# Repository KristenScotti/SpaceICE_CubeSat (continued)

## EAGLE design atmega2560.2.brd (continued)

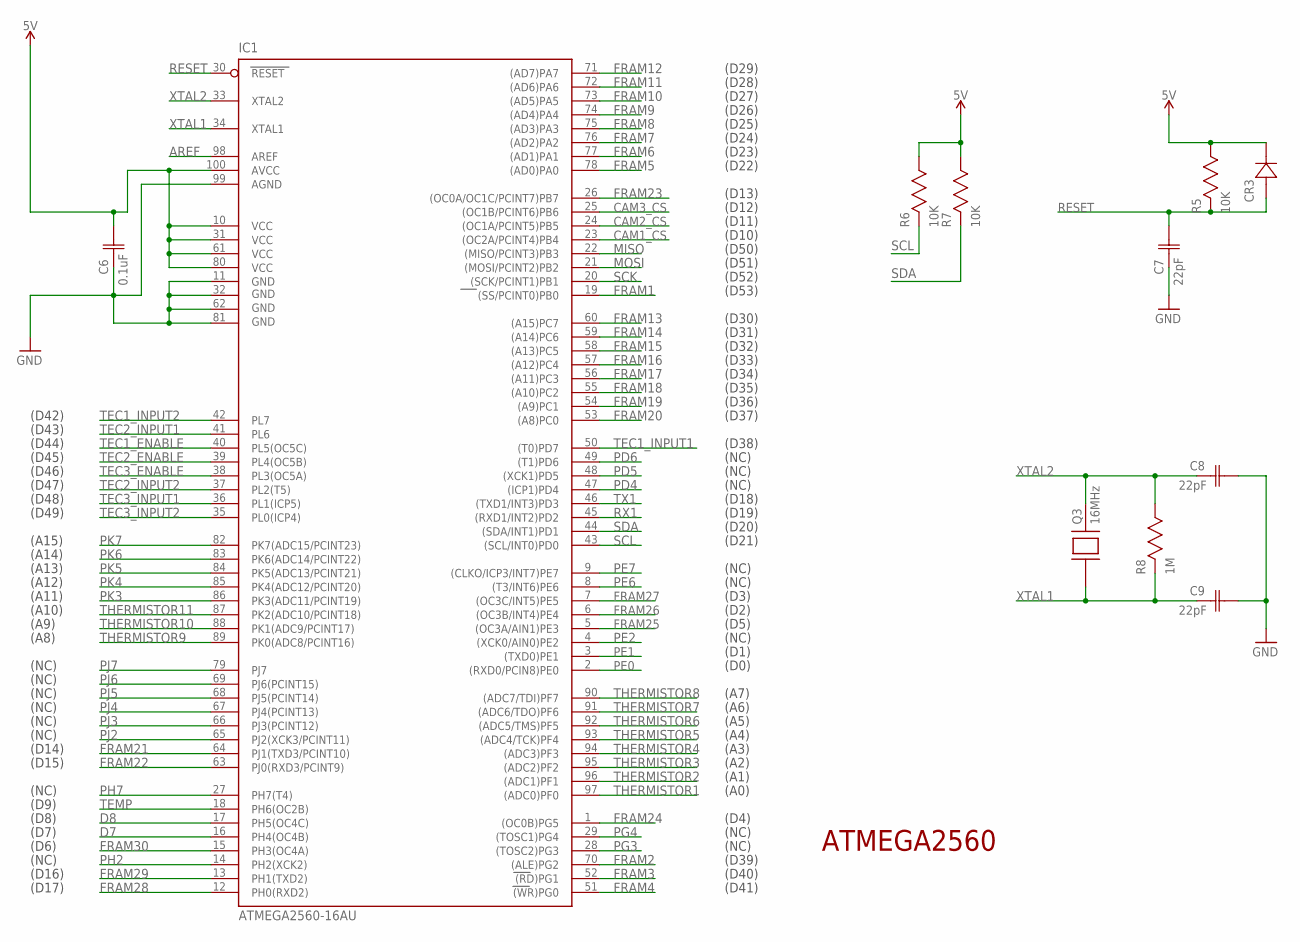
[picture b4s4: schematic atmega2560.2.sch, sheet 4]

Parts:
C6: 0.1uF; CAP_01
C7, C8, C9: 22pF; CC0805N
CR3: DIODE_600V_3A
IC1: ATMEGA2560-16AU; TQFP100
Q3: 16MHz; OSCILLATOR
R5, R6, R7: 10K; RC0603N
R8: 1M; RC0603N

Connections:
5V: C6.2, CR3.1 (12), IC1.10 (VCC), IC1.31 (VCC1), IC1.61 (VCC2), IC1.80 (VCC3), IC1.100 (AVCC), R5.1 (11), R6.1 (11), R7.1 (11); also elsewhere on the board
AREF: IC1.98 (AREF); also elsewhere on the board
CAM1_CS: IC1.23 ((OC2A/PCINT4)PB4); also elsewhere on the board
CAM2_CS: IC1.24 ((OC1A/PCINT5)PB5); also elsewhere on the board
CAM3_CS: IC1.25 ((OC1B/PCINT6)PB6); also elsewhere on the board
D7: IC1.16 (PH4(OC4B)); also elsewhere on the board
D8: IC1.17 (PH5(OC4C)); also elsewhere on the board
FRAM1: IC1.19 ((SS/PCINT0)PB0); also elsewhere on the board
FRAM2: IC1.70 ((ALE)PG2); also elsewhere on the board
FRAM3: IC1.52 ((RD)PG1); also elsewhere on the board
FRAM4: IC1.51 ((WR)PG0); also elsewhere on the board
FRAM5: IC1.78 ((AD0)PA0); also elsewhere on the board
FRAM6: IC1.77 ((AD1)PA1); also elsewhere on the board
FRAM7: IC1.76 ((AD2)PA2); also elsewhere on the board
FRAM8: IC1.75 ((AD3)PA3); also elsewhere on the board
FRAM9: IC1.74 ((AD4)PA4); also elsewhere on the board
FRAM10: IC1.73 ((AD5)PA5); also elsewhere on the board
FRAM11: IC1.72 ((AD6)PA6); also elsewhere on the board
FRAM12: IC1.71 ((AD7)PA7); also elsewhere on the board
FRAM13: IC1.60 ((A15)PC7); also elsewhere on the board
FRAM14: IC1.59 ((A14)PC6); also elsewhere on the board
FRAM15: IC1.58 ((A13)PC5); also elsewhere on the board
FRAM16: IC1.57 ((A12)PC4); also elsewhere on the board
FRAM17: IC1.56 ((A11)PC3); also elsewhere on the board
FRAM18: IC1.55 ((A10)PC2); also elsewhere on the board
FRAM19: IC1.54 ((A9)PC1); also elsewhere on the board
FRAM20: IC1.53 ((A8)PC0); also elsewhere on the board
FRAM21: IC1.64 (PJ1(TXD3/PCINT10)); also elsewhere on the board
FRAM22: IC1.63 (PJ0(RXD3/PCINT9)); also elsewhere on the board
FRAM23: IC1.26 ((OC0A/OC1C/PCINT7)PB7); also elsewhere on the board
FRAM24: IC1.1 ((OC0B)PG5); also elsewhere on the board
FRAM25: IC1.5 ((OC3A/AIN1)PE3); also elsewhere on the board
FRAM26: IC1.6 ((OC3B/INT4)PE4); also elsewhere on the board
FRAM27: IC1.7 ((OC3C/INT5)PE5); also elsewhere on the board
FRAM28: IC1.12 (PH0(RXD2)); also elsewhere on the board
FRAM29: IC1.13 (PH1(TXD2)); also elsewhere on the board
FRAM30: IC1.15 (PH3(OC4A)); also elsewhere on the board
GND: C6.1, C7.1, C8.2, C9.2, IC1.11 (GND), IC1.32 (GND1), IC1.62 (GND2), IC1.81 (GND3), IC1.99 (AGND); also elsewhere on the board
MISO: IC1.22 ((MISO/PCINT3)PB3); also elsewhere on the board
MOSI: IC1.21 ((MOSI/PCINT2)PB2); also elsewhere on the board
PD4: IC1.47 ((ICP1)PD4)
PD5: IC1.48 ((XCK1)PD5)
PD6: IC1.49 ((T1)PD6)
PE0: IC1.2 ((RXD0/PCIN8)PE0); also elsewhere on the board
PE1: IC1.3 ((TXD0)PE1); also elsewhere on the board
PE2: IC1.4 ((XCK0/AIN0)PE2)
PE6: IC1.8 ((T3/INT6)PE6)
PE7: IC1.9 ((CLKO/ICP3/INT7)PE7)
PG3: IC1.28 ((TOSC2)PG3)
PG4: IC1.29 ((TOSC1)PG4)
PH2: IC1.14 (PH2(XCK2))
PH7: IC1.27 (PH7(T4))
PJ2: IC1.65 (PJ2(XCK3/PCINT11))
PJ3: IC1.66 (PJ3(PCINT12))
PJ4: IC1.67 (PJ4(PCINT13))
PJ5: IC1.68 (PJ5(PCINT14))
PJ6: IC1.69 (PJ6(PCINT15))
PJ7: IC1.79 (PJ7)
PK3: IC1.86 (PK3(ADC11/PCINT19)); also elsewhere on the board
PK4: IC1.85 (PK4(ADC12/PCINT20)); also elsewhere on the board
PK5: IC1.84 (PK5(ADC13/PCINT21)); also elsewhere on the board
PK6: IC1.83 (PK6(ADC14/PCINT22)); also elsewhere on the board
PK7: IC1.82 (PK7(ADC15/PCINT23)); also elsewhere on the board
RESET: C7.2, CR3.2 (21), IC1.30 (RESET), R5.2 (22); also elsewhere on the board
RX1: IC1.45 ((RXD1/INT2)PD2); also elsewhere on the board
SCK: IC1.20 ((SCK/PCINT1)PB1); also elsewhere on the board
SCL: IC1.43 ((SCL/INT0)PD0), R6.2 (22); also elsewhere on the board
SDA: IC1.44 ((SDA/INT1)PD1), R7.2 (22); also elsewhere on the board
TEC1_ENABLE: IC1.40 (PL5(OC5C)); also elsewhere on the board
TEC1_INPUT1: IC1.50 ((T0)PD7); also elsewhere on the board
TEC1_INPUT2: IC1.42 (PL7); also elsewhere on the board
TEC2_ENABLE: IC1.39 (PL4(OC5B)); also elsewhere on the board
TEC2_INPUT1: IC1.41 (PL6); also elsewhere on the board
TEC2_INPUT2: IC1.37 (PL2(T5)); also elsewhere on the board
TEC3_ENABLE: IC1.38 (PL3(OC5A)); also elsewhere on the board
TEC3_INPUT1: IC1.36 (PL1(ICP5)); also elsewhere on the board
TEC3_INPUT2: IC1.35 (PL0(ICP4)); also elsewhere on the board
TEMP: IC1.18 (PH6(OC2B)); also elsewhere on the board
THERMISTOR1: IC1.97 ((ADC0)PF0); also elsewhere on the board
THERMISTOR2: IC1.96 ((ADC1)PF1); also elsewhere on the board
THERMISTOR3: IC1.95 ((ADC2)PF2); also elsewhere on the board
THERMISTOR4: IC1.94 ((ADC3)PF3); also elsewhere on the board
THERMISTOR5: IC1.93 ((ADC4/TCK)PF4); also elsewhere on the board
THERMISTOR6: IC1.92 ((ADC5/TMS)PF5); also elsewhere on the board
THERMISTOR7: IC1.91 ((ADC6/TDO)PF6); also elsewhere on the board
THERMISTOR8: IC1.90 ((ADC7/TDI)PF7); also elsewhere on the board
THERMISTOR9: IC1.89 (PK0(ADC8/PCINT16)); also elsewhere on the board
THERMISTOR10: IC1.88 (PK1(ADC9/PCINT17)); also elsewhere on the board
THERMISTOR11: IC1.87 (PK2(ADC10/PCINT18)); also elsewhere on the board
TX1: IC1.46 ((TXD1/INT3)PD3); also elsewhere on the board
XTAL1: C9.1, IC1.34 (XTAL1), Q3.1, R8.2 (22)
XTAL2: C8.1, IC1.33 (XTAL2), Q3.2, R8.1 (11)

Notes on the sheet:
ATMEGA2560
(D4)
(D39)
(D40)
(D41)
(A0)
(D0)
(D3)
(D2)
(D5)
(D1)
(D21)
(D18)
(D19)
(D20)
(NC)
(D38)
(D37)
(D32)
(D33)
(D34)
(D35)
(D36)
(D31)
(D30)
(D53)
(D11)
(D10)
(D50)
(D51)
(D52)
(D12)
(D13)
(D22)
(D27)
(D26)
(D25)
(D24)
(D23)
(D28)

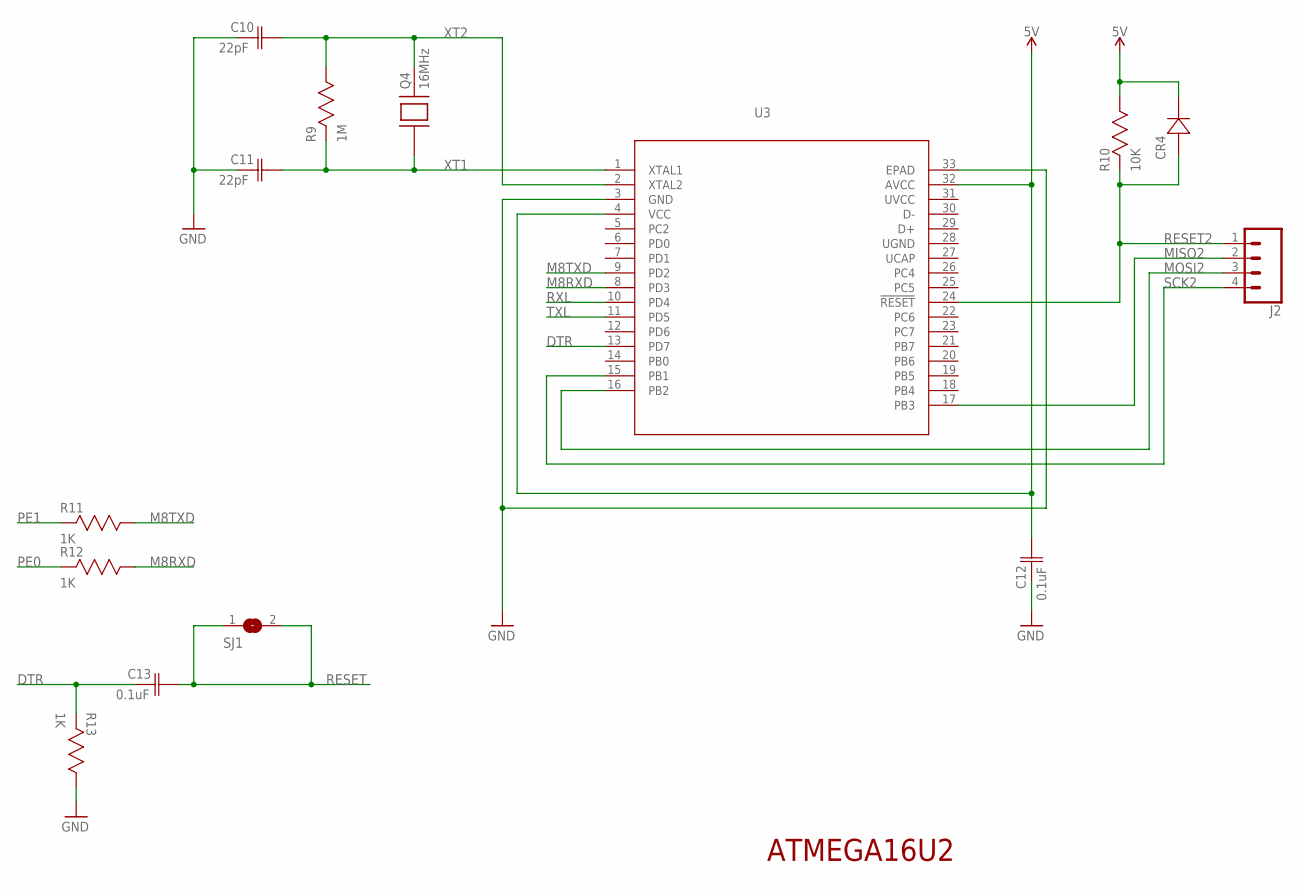
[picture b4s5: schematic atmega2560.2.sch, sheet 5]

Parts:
C10, C11: 22pF; CC0805N
C12, C13: 0.1uF; CAP_01
CR4: DIODE_600V_3A
J2: CONN_04; 1X04
Q4: 16MHz; OSCILLATOR
R9: 1M; RC0603N
R10: 10K; RC0603N
R11, R12, R13: 1K; RC0603N
SJ1: SJ
U3: ATMEGA16U2-MU; 32M1-A

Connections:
5V: C12.2, CR4.1 (12), R10.1 (11), U3.4 (VCC), U3.32 (AVCC); also elsewhere on the board
DTR: C13.1, R13.2 (22), U3.13 (PD7)
GND: C10.1, C11.1, C12.1, R13.1 (11), U3.3 (GND), U3.33 (EPAD); also elsewhere on the board
M8RXD: R12.1 (11), U3.8 (PD3)
M8TXD: R11.1 (11), U3.9 (PD2)
MISO2: J2.2, U3.17 (PB3)
MOSI2: J2.3, U3.16 (PB2)
PE0: R12.2 (22); also elsewhere on the board
PE1: R11.2 (22); also elsewhere on the board
RESET: C13.2, SJ1.1, SJ1.2; also elsewhere on the board
RESET2: CR4.2 (21), J2.1, R10.2 (22), U3.24 (!RESET)
RXL: U3.10 (PD4)
SCK2: J2.4, U3.15 (PB1)
TXL: U3.11 (PD5)
UGND: U3.28 (UGND)
UVCC: U3.31 (UVCC)
XT1: C11.2, Q4.1, R9.2 (22), U3.1 (XTAL1)
XT2: C10.2, Q4.2, R9.1 (11), U3.2 (XTAL2)

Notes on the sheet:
ATMEGA16U2

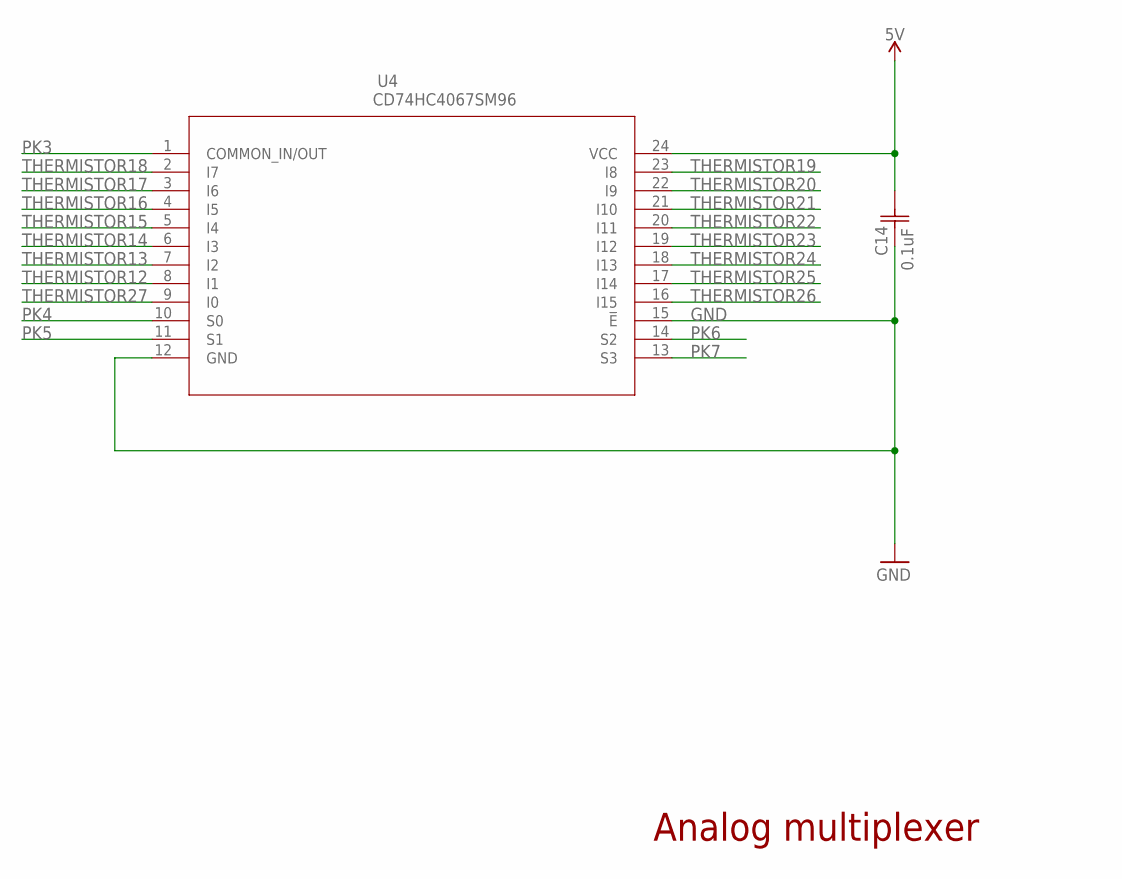
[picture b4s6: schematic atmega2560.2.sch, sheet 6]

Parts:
C14: 0.1uF; CAP_01
U4: CD74HC4067SM96; DB24

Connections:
5V: C14.2, U4.24 (VCC); also elsewhere on the board
GND: C14.1, U4.12 (GND), U4.15 (!E); also elsewhere on the board
PK3: U4.1 (COMMON_IN/OUT); also elsewhere on the board
PK4: U4.10 (S0); also elsewhere on the board
PK5: U4.11 (S1); also elsewhere on the board
PK6: U4.14 (S2); also elsewhere on the board
PK7: U4.13 (S3); also elsewhere on the board
THERMISTOR12: U4.8 (I1); also elsewhere on the board
THERMISTOR13: U4.7 (I2); also elsewhere on the board
THERMISTOR14: U4.6 (I3); also elsewhere on the board
THERMISTOR15: U4.5 (I4); also elsewhere on the board
THERMISTOR16: U4.4 (I5); also elsewhere on the board
THERMISTOR17: U4.3 (I6); also elsewhere on the board
THERMISTOR18: U4.2 (I7); also elsewhere on the board
THERMISTOR19: U4.23 (I8); also elsewhere on the board
THERMISTOR20: U4.22 (I9); also elsewhere on the board
THERMISTOR21: U4.21 (I10); also elsewhere on the board
THERMISTOR22: U4.20 (I11); also elsewhere on the board
THERMISTOR23: U4.19 (I12); also elsewhere on the board
THERMISTOR24: U4.18 (I13); also elsewhere on the board
THERMISTOR25: U4.17 (I14); also elsewhere on the board
THERMISTOR26: U4.16 (I15); also elsewhere on the board
THERMISTOR27: U4.9 (I0); also elsewhere on the board

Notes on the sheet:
Analog multiplexer

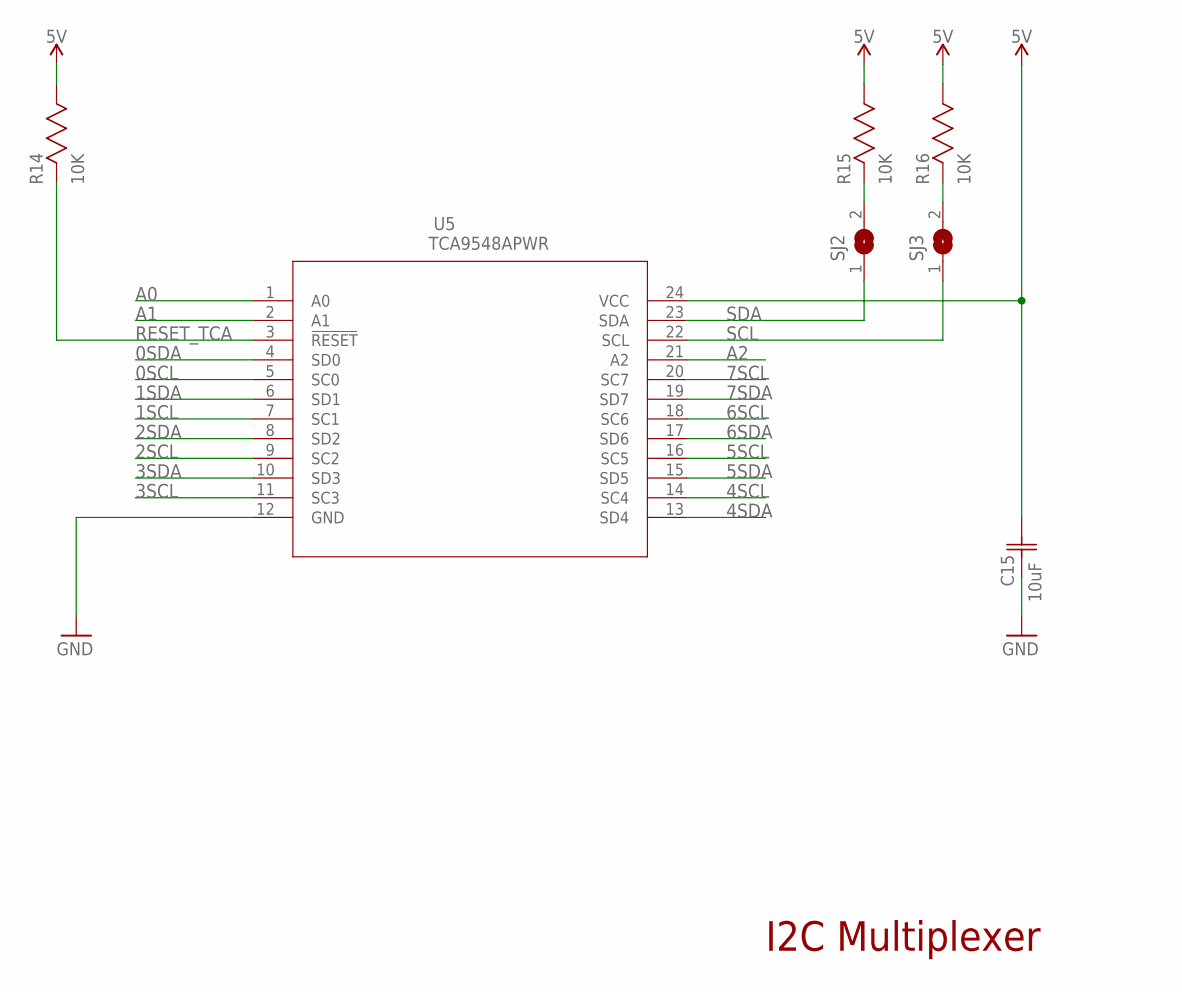
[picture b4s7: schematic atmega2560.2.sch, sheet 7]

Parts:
C15: 10uF; CAP_GRM219R61A106KE44D
R14, R15, R16: 10K; RC0603N
SJ2, SJ3: SOLDERJUMPERCLOSED; SOLDERJUMPER_CLOSEDWIRE
U5: TCA9548APWR; PW24

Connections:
0SCL: U5.5 (SC0); also elsewhere on the board
0SDA: U5.4 (SD0); also elsewhere on the board
1SCL: U5.7 (SC1); also elsewhere on the board
1SDA: U5.6 (SD1); also elsewhere on the board
2SCL: U5.9 (SC2); also elsewhere on the board
2SDA: U5.8 (SD2); also elsewhere on the board
3SCL: U5.11 (SC3)
3SDA: U5.10 (SD3)
4SCL: U5.14 (SC4)
4SDA: U5.13 (SD4)
5SCL: U5.16 (SC5)
5SDA: U5.15 (SD5)
5V: C15.2, R14.1 (11), R15.1 (11), R16.1 (11), U5.24 (VCC); also elsewhere on the board
6SCL: U5.18 (SC6)
6SDA: U5.17 (SD6)
7SCL: U5.20 (SC7)
7SDA: U5.19 (SD7)
A0: U5.1 (A0)
A1: U5.2 (A1)
A2: U5.21 (A2)
GND: C15.1, U5.12 (GND); also elsewhere on the board
unnamed: R15.2 (22), SJ2.2
unnamed: R16.2 (22), SJ3.2
RESET_TCA: R14.2 (22), U5.3 (!RESET)
SCL: SJ3.1, U5.22 (SCL); also elsewhere on the board
SDA: SJ2.1, U5.23 (SDA); also elsewhere on the board

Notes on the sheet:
I2C Multiplexer

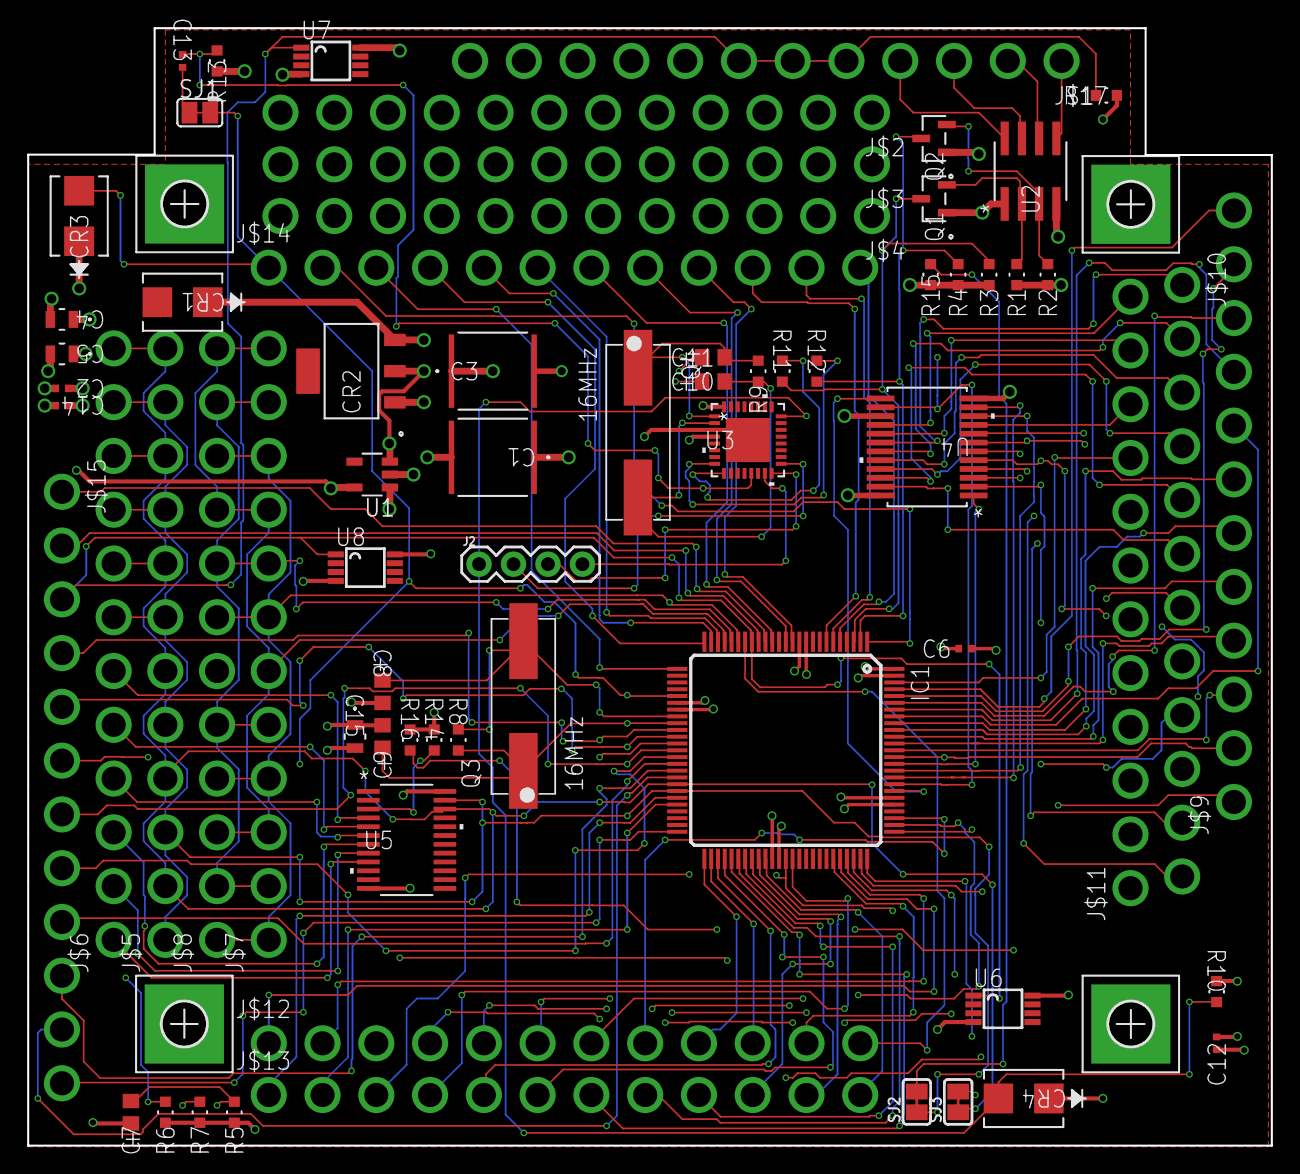
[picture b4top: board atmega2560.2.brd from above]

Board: 4 copper layers, 91.6 x 82.3 mm, 72 parts (0 on the bottom side), 118 nets.

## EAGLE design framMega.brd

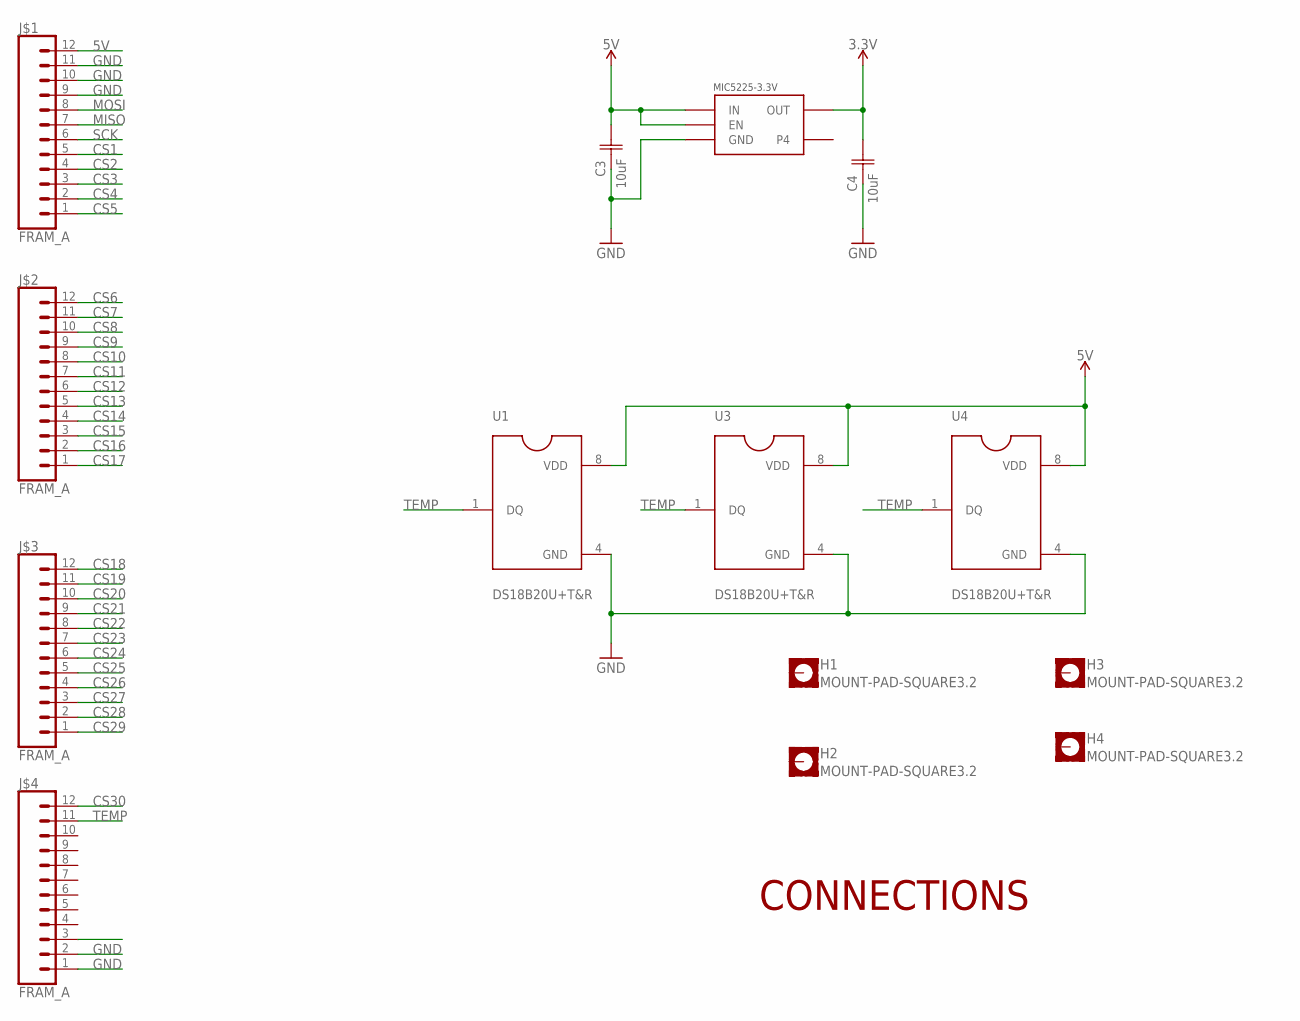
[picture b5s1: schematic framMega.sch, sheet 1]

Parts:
C3, C4: 10uF; CAP_GRM219R61A106KE44D
H1, H2, H3, H4: MOUNT-PAD-SQUARE3.2; 3,2-PAD-SQUARE
J$1, J$2, J$3, J$4: FRAM_A; WIREWRAPPOST
U1, U3, U4: DS18B20U+T&R; SOP65P500X110-8N
U2: MIC5225; SOT23-5

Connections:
3.3V: C4.2, U2.OUT; also elsewhere on the board
5V: C3.2, J$1.12, J$4.3, U1.8 (VDD), U2.EN, U2.IN, U3.8 (VDD), U4.8 (VDD); also elsewhere on the board
CS1: J$1.5; also elsewhere on the board
CS2: J$1.4; also elsewhere on the board
CS3: J$1.3; also elsewhere on the board
CS4: J$1.2; also elsewhere on the board
CS5: J$1.1; also elsewhere on the board
CS6: J$2.12; also elsewhere on the board
CS7: J$2.11; also elsewhere on the board
CS8: J$2.10; also elsewhere on the board
CS9: J$2.9; also elsewhere on the board
CS10: J$2.8; also elsewhere on the board
CS11: J$2.7; also elsewhere on the board
CS12: J$2.6; also elsewhere on the board
CS13: J$2.5; also elsewhere on the board
CS14: J$2.4; also elsewhere on the board
CS15: J$2.3; also elsewhere on the board
CS16: J$2.2; also elsewhere on the board
CS17: J$2.1; also elsewhere on the board
CS18: J$3.12; also elsewhere on the board
CS19: J$3.11; also elsewhere on the board
CS20: J$3.10; also elsewhere on the board
CS21: J$3.9; also elsewhere on the board
CS22: J$3.8; also elsewhere on the board
CS23: J$3.7; also elsewhere on the board
CS24: J$3.6; also elsewhere on the board
CS25: J$3.5; also elsewhere on the board
CS26: J$3.4; also elsewhere on the board
CS27: J$3.3; also elsewhere on the board
CS28: J$3.2; also elsewhere on the board
CS29: J$3.1; also elsewhere on the board
CS30: J$4.12; also elsewhere on the board
GND: C3.1, C4.1, J$1.9, J$1.10, J$1.11, J$4.1, J$4.2, U1.4 (GND), U2.GND, U3.4 (GND), U4.4 (GND); also elsewhere on the board
MISO: J$1.7; also elsewhere on the board
MOSI: J$1.8; also elsewhere on the board
SCK: J$1.6; also elsewhere on the board
TEMP: J$4.11, U1.1 (DQ), U3.1 (DQ), U4.1 (DQ)

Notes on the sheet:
CONNECTIONS

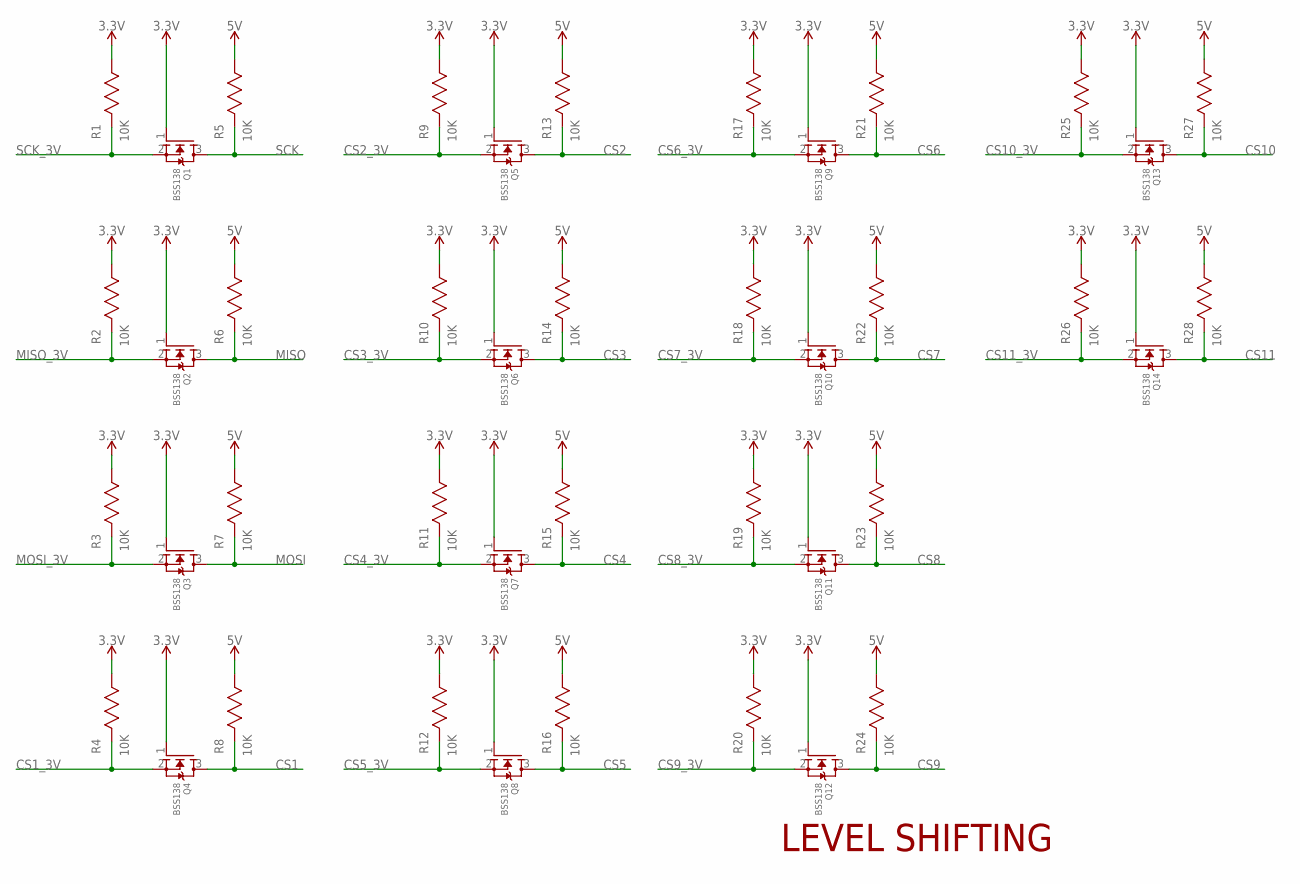
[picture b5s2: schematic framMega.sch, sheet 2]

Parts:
Q1, Q2, Q3, Q4, Q5, Q6, Q7, Q8, Q9, Q10, Q11, Q12, Q13, Q14: BSS138; SOT23-WIDE
R1, R2, R3, R4, R5, R6, R7, R8, R9, R10, R11, R12, R13, R14, R15, R16, R17, R18, R19, R20, R21, R22, R23, R24, R25, R26, R27, R28: 10K; RC0603N

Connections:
3.3V: Q1.1 (G), Q2.1 (G), Q3.1 (G), Q4.1 (G), Q5.1 (G), Q6.1 (G), Q7.1 (G), Q8.1 (G), Q9.1 (G), Q10.1 (G), Q11.1 (G), Q12.1 (G), Q13.1 (G), Q14.1 (G), R1.1 (11), R2.1 (11), R3.1 (11), R4.1 (11), R9.1 (11), R10.1 (11), R11.1 (11), R12.1 (11), R17.1 (11), R18.1 (11), R19.1 (11), R20.1 (11), R25.1 (11), R26.1 (11); also elsewhere on the board
5V: R5.1 (11), R6.1 (11), R7.1 (11), R8.1 (11), R13.1 (11), R14.1 (11), R15.1 (11), R16.1 (11), R21.1 (11), R22.1 (11), R23.1 (11), R24.1 (11), R27.1 (11), R28.1 (11); also elsewhere on the board
CS1: Q4.3 (D), R8.2 (22); also elsewhere on the board
CS1_3V: Q4.2 (S), R4.2 (22); also elsewhere on the board
CS2: Q5.3 (D), R13.2 (22); also elsewhere on the board
CS2_3V: Q5.2 (S), R9.2 (22); also elsewhere on the board
CS3: Q6.3 (D), R14.2 (22); also elsewhere on the board
CS3_3V: Q6.2 (S), R10.2 (22); also elsewhere on the board
CS4: Q7.3 (D), R15.2 (22); also elsewhere on the board
CS4_3V: Q7.2 (S), R11.2 (22); also elsewhere on the board
CS5: Q8.3 (D), R16.2 (22); also elsewhere on the board
CS5_3V: Q8.2 (S), R12.2 (22); also elsewhere on the board
CS6: Q9.3 (D), R21.2 (22); also elsewhere on the board
CS6_3V: Q9.2 (S), R17.2 (22); also elsewhere on the board
CS7: Q10.3 (D), R22.2 (22); also elsewhere on the board
CS7_3V: Q10.2 (S), R18.2 (22); also elsewhere on the board
CS8: Q11.3 (D), R23.2 (22); also elsewhere on the board
CS8_3V: Q11.2 (S), R19.2 (22); also elsewhere on the board
CS9: Q12.3 (D), R24.2 (22); also elsewhere on the board
CS9_3V: Q12.2 (S), R20.2 (22); also elsewhere on the board
CS10: Q13.3 (D), R27.2 (22); also elsewhere on the board
CS10_3V: Q13.2 (S), R25.2 (22); also elsewhere on the board
CS11: Q14.3 (D), R28.2 (22); also elsewhere on the board
CS11_3V: Q14.2 (S), R26.2 (22); also elsewhere on the board
MISO: Q2.3 (D), R6.2 (22); also elsewhere on the board
MISO_3V: Q2.2 (S), R2.2 (22); also elsewhere on the board
MOSI: Q3.3 (D), R7.2 (22); also elsewhere on the board
MOSI_3V: Q3.2 (S), R3.2 (22); also elsewhere on the board
SCK: Q1.3 (D), R5.2 (22); also elsewhere on the board
SCK_3V: Q1.2 (S), R1.2 (22); also elsewhere on the board

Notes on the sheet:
LEVEL SHIFTING

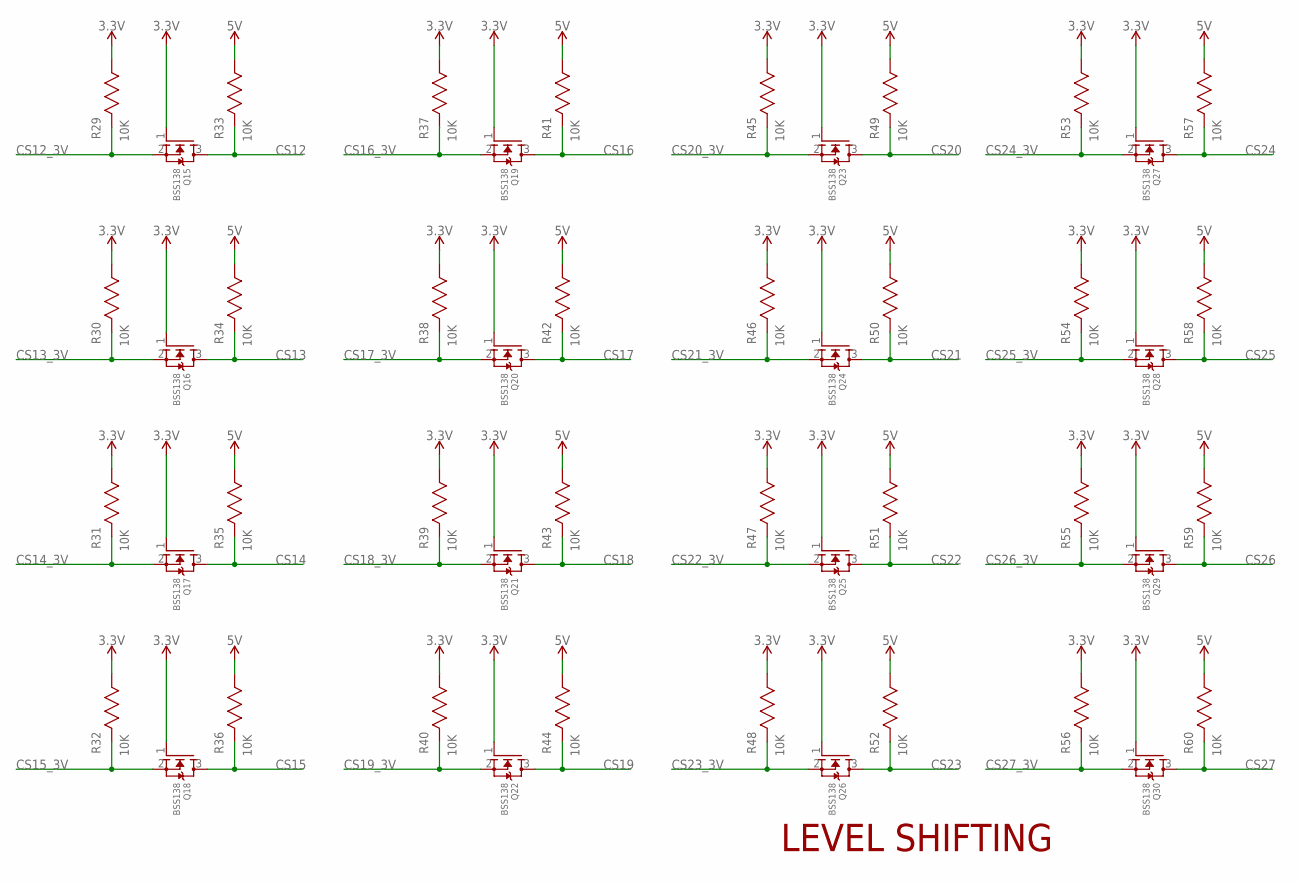
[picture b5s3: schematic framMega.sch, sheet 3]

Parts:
Q15, Q16, Q17, Q18, Q19, Q20, Q21, Q22, Q23, Q24, Q25, Q26, Q27, Q28, Q29, Q30: BSS138; SOT23-WIDE
R29, R30, R31, R32, R33, R34, R35, R36, R37, R38, R39, R40, R41, R42, R43, R44, R45, R46, R47, R48, R49, R50, R51, R52, R53, R54, R55, R56, R57, R58, R59, R60: 10K; RC0603N

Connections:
3.3V: Q15.1 (G), Q16.1 (G), Q17.1 (G), Q18.1 (G), Q19.1 (G), Q20.1 (G), Q21.1 (G), Q22.1 (G), Q23.1 (G), Q24.1 (G), Q25.1 (G), Q26.1 (G), Q27.1 (G), Q28.1 (G), Q29.1 (G), Q30.1 (G), R29.1 (11), R30.1 (11), R31.1 (11), R32.1 (11), R37.1 (11), R38.1 (11), R39.1 (11), R40.1 (11), R45.1 (11), R46.1 (11), R47.1 (11), R48.1 (11), R53.1 (11), R54.1 (11), R55.1 (11), R56.1 (11); also elsewhere on the board
5V: R33.1 (11), R34.1 (11), R35.1 (11), R36.1 (11), R41.1 (11), R42.1 (11), R43.1 (11), R44.1 (11), R49.1 (11), R50.1 (11), R51.1 (11), R52.1 (11), R57.1 (11), R58.1 (11), R59.1 (11), R60.1 (11); also elsewhere on the board
CS12: Q15.3 (D), R33.2 (22); also elsewhere on the board
CS12_3V: Q15.2 (S), R29.2 (22); also elsewhere on the board
CS13: Q16.3 (D), R34.2 (22); also elsewhere on the board
CS13_3V: Q16.2 (S), R30.2 (22); also elsewhere on the board
CS14: Q17.3 (D), R35.2 (22); also elsewhere on the board
CS14_3V: Q17.2 (S), R31.2 (22); also elsewhere on the board
CS15: Q18.3 (D), R36.2 (22); also elsewhere on the board
CS15_3V: Q18.2 (S), R32.2 (22); also elsewhere on the board
CS16: Q19.3 (D), R41.2 (22); also elsewhere on the board
CS16_3V: Q19.2 (S), R37.2 (22); also elsewhere on the board
CS17: Q20.3 (D), R42.2 (22); also elsewhere on the board
CS17_3V: Q20.2 (S), R38.2 (22); also elsewhere on the board
CS18: Q21.3 (D), R43.2 (22); also elsewhere on the board
CS18_3V: Q21.2 (S), R39.2 (22); also elsewhere on the board
CS19: Q22.3 (D), R44.2 (22); also elsewhere on the board
CS19_3V: Q22.2 (S), R40.2 (22); also elsewhere on the board
CS20: Q23.3 (D), R49.2 (22); also elsewhere on the board
CS20_3V: Q23.2 (S), R45.2 (22); also elsewhere on the board
CS21: Q24.3 (D), R50.2 (22); also elsewhere on the board
CS21_3V: Q24.2 (S), R46.2 (22); also elsewhere on the board
CS22: Q25.3 (D), R51.2 (22); also elsewhere on the board
CS22_3V: Q25.2 (S), R47.2 (22); also elsewhere on the board
CS23: Q26.3 (D), R52.2 (22); also elsewhere on the board
CS23_3V: Q26.2 (S), R48.2 (22); also elsewhere on the board
CS24: Q27.3 (D), R57.2 (22); also elsewhere on the board
CS24_3V: Q27.2 (S), R53.2 (22); also elsewhere on the board
CS25: Q28.3 (D), R58.2 (22); also elsewhere on the board
CS25_3V: Q28.2 (S), R54.2 (22); also elsewhere on the board
CS26: Q29.3 (D), R59.2 (22); also elsewhere on the board
CS26_3V: Q29.2 (S), R55.2 (22); also elsewhere on the board
CS27: Q30.3 (D), R60.2 (22); also elsewhere on the board
CS27_3V: Q30.2 (S), R56.2 (22); also elsewhere on the board

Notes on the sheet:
LEVEL SHIFTING

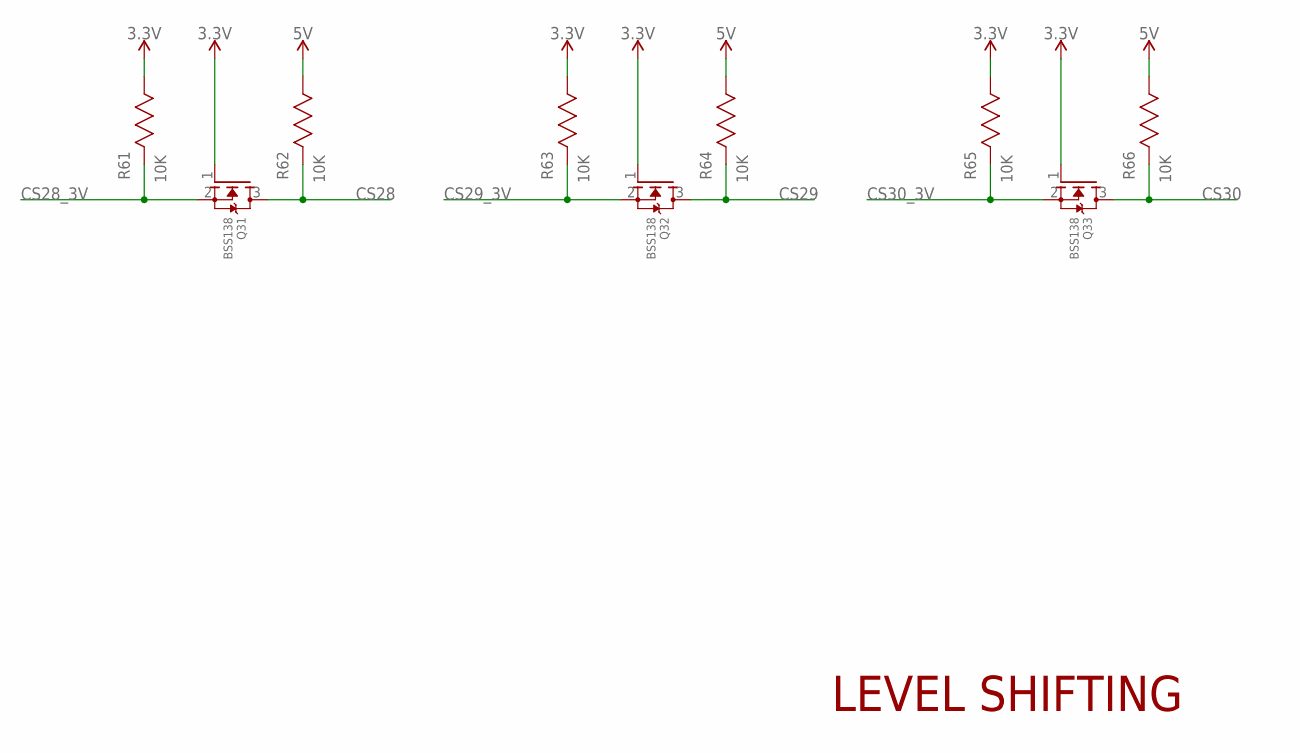
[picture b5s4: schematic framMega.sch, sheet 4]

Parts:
Q31, Q32, Q33: BSS138; SOT23-WIDE
R61, R62, R63, R64, R65, R66: 10K; RC0603N

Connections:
3.3V: Q31.1 (G), Q32.1 (G), Q33.1 (G), R61.1 (11), R63.1 (11), R65.1 (11); also elsewhere on the board
5V: R62.1 (11), R64.1 (11), R66.1 (11); also elsewhere on the board
CS28: Q31.3 (D), R62.2 (22); also elsewhere on the board
CS28_3V: Q31.2 (S), R61.2 (22); also elsewhere on the board
CS29: Q32.3 (D), R64.2 (22); also elsewhere on the board
CS29_3V: Q32.2 (S), R63.2 (22); also elsewhere on the board
CS30: Q33.3 (D), R66.2 (22); also elsewhere on the board
CS30_3V: Q33.2 (S), R65.2 (22); also elsewhere on the board

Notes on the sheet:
LEVEL SHIFTING

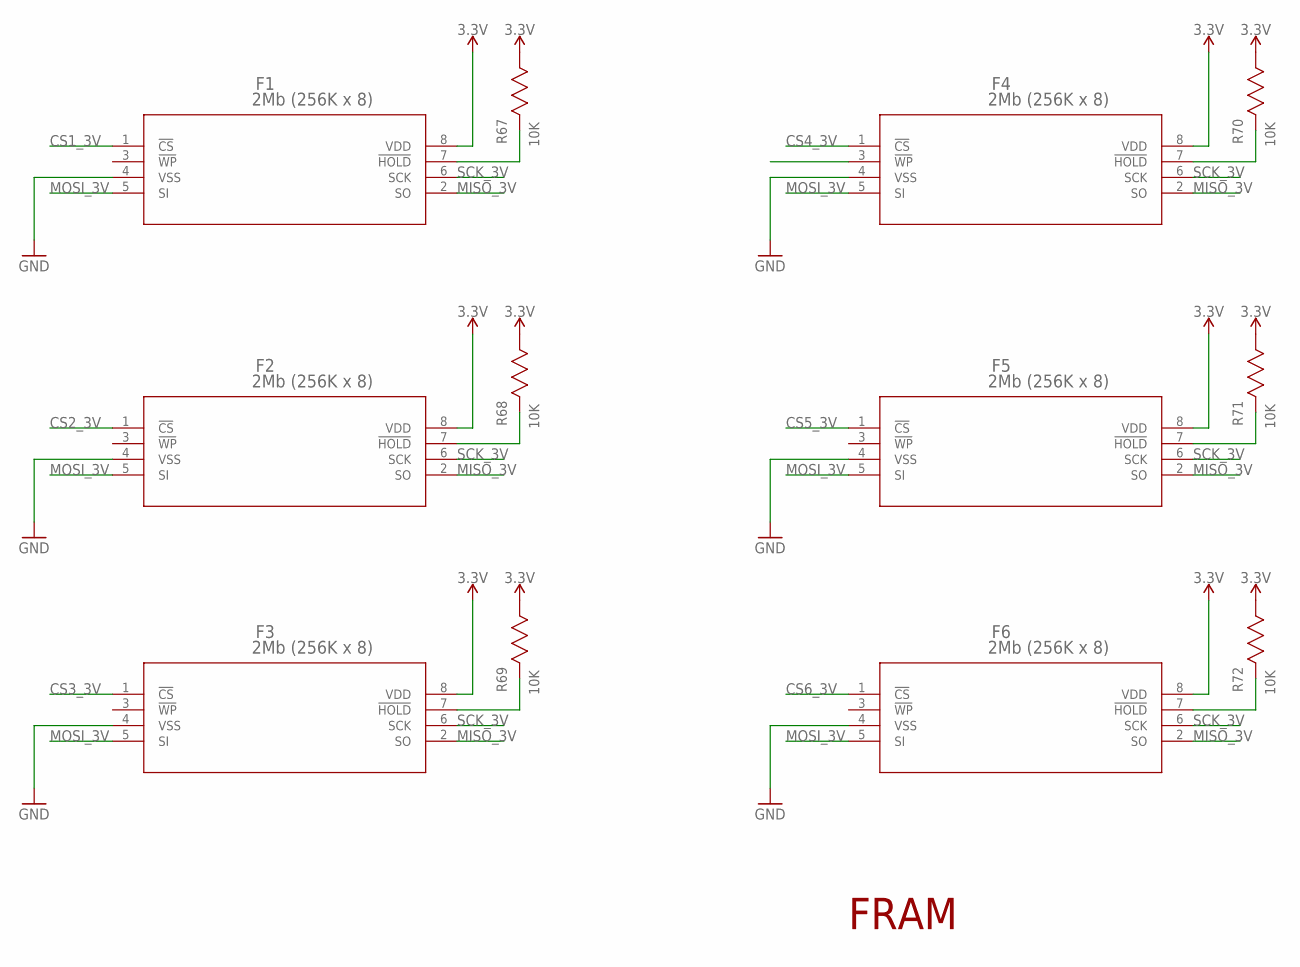
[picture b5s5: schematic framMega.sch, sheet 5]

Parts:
F1, F2, F3, F4, F5, F6: 2Mb (256K x 8); FRAM_MB85RS2MTA_FPT-8P-M09
R67, R68, R69, R70, R71, R72: 10K; RC0603N

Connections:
3.3V: F1.8 (VDD), F2.8 (VDD), F3.8 (VDD), F4.8 (VDD), F5.8 (VDD), F6.8 (VDD), R67.1 (11), R68.1 (11), R69.1 (11), R70.1 (11), R71.1 (11), R72.1 (11); also elsewhere on the board
CS1_3V: F1.1 (!CS); also elsewhere on the board
CS2_3V: F2.1 (!CS); also elsewhere on the board
CS3_3V: F3.1 (!CS); also elsewhere on the board
CS4_3V: F4.1 (!CS); also elsewhere on the board
CS5_3V: F5.1 (!CS); also elsewhere on the board
CS6_3V: F6.1 (!CS); also elsewhere on the board
GND: F1.4 (VSS), F2.4 (VSS), F3.4 (VSS), F4.4 (VSS), F5.4 (VSS), F6.4 (VSS); also elsewhere on the board
MISO_3V: F1.2 (SO), F2.2 (SO), F3.2 (SO), F4.2 (SO), F5.2 (SO), F6.2 (SO); also elsewhere on the board
MOSI_3V: F1.5 (SI), F2.5 (SI), F3.5 (SI), F4.5 (SI), F5.5 (SI), F6.5 (SI); also elsewhere on the board
unnamed: F1.7 (!HOLD), R67.2 (22)
unnamed: F4.7 (!HOLD), R70.2 (22)
unnamed: F2.7 (!HOLD), R68.2 (22)
unnamed: F5.7 (!HOLD), R71.2 (22)
unnamed: F3.7 (!HOLD), R69.2 (22)
unnamed: F6.7 (!HOLD), R72.2 (22)
SCK_3V: F1.6 (SCK), F2.6 (SCK), F3.6 (SCK), F4.6 (SCK), F5.6 (SCK), F6.6 (SCK); also elsewhere on the board

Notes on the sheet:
FRAM
